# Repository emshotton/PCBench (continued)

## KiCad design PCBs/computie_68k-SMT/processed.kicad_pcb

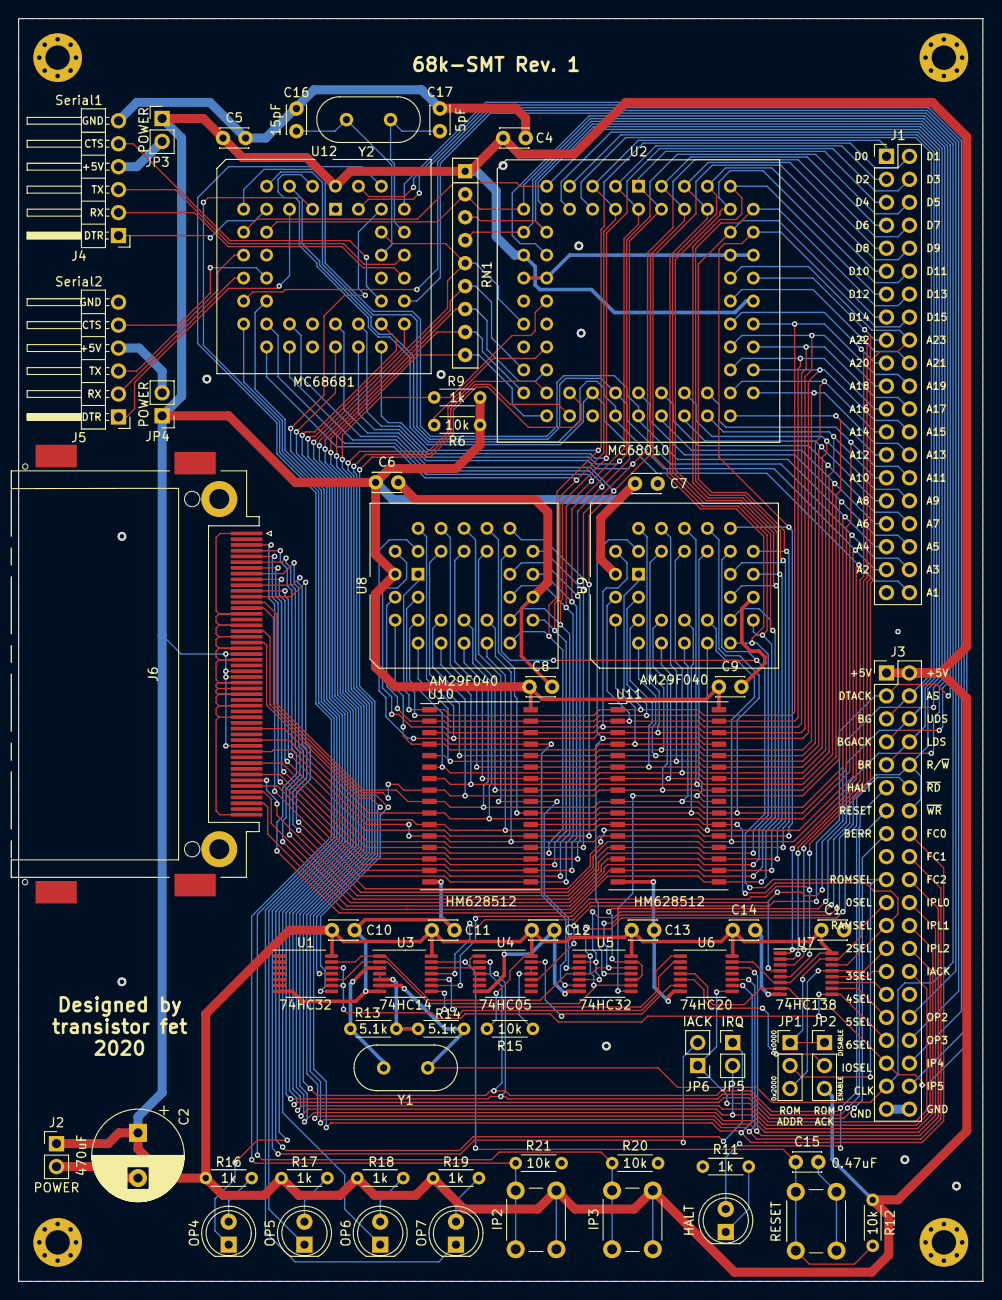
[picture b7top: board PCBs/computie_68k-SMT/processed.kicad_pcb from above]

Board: 2 copper layers, 106.7 x 139.7 mm, 68 parts (0 on the bottom side), 115 nets.

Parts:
C1, C4, C5, C6, C7, C8, C9, C10, C11, C12, C13, C14: 0.1uF; C_Disc_D3.0mm_W2.0mm_P2.50mm
C2: 470uF; CP_Radial_D10.0mm_P5.00mm
C15: 0.47uF; C_Disc_D3.0mm_W2.0mm_P2.50mm
C16: 15pF; C_Disc_D3.0mm_W2.0mm_P2.50mm
C17: 5pF; C_Disc_D3.0mm_W2.0mm_P2.50mm
D1: HALT; LED_D5.0mm
D2: OP4; LED_D5.0mm
D3: OP5; LED_D5.0mm
D4: OP6; LED_D5.0mm
D5: OP7; LED_D5.0mm
H1, H2, H3, H4: .; MountingHole_2.7mm_Pad_Via
J1: ADBUS; PinHeader_2x20_P2.54mm_Vertical
J2: POWER; PinHeader_1x02_P2.54mm_Vertical
J3: SIGBUS; PinHeader_2x20_P2.54mm_Vertical
J4: Serial1; PinHeader_1x06_P2.54mm_Horizontal
J5: Serial2; PinHeader_1x06_P2.54mm_Horizontal
J6: CompactFlash; CF-Card_3M_N7E50-Q516RB-40
JP1: ROMJMP; PinHeader_1x03_P2.54mm_Vertical
JP2: ROMACK; PinHeader_1x03_P2.54mm_Vertical
JP3, JP4: POWER; PinHeader_1x02_P2.54mm_Vertical
JP5: IRQ; PinHeader_1x02_P2.54mm_Vertical
JP6: IACK; PinHeader_1x02_P2.54mm_Vertical
R6, R12, R15, R20, R21: 10k; R_Axial_DIN0204_L3.6mm_D1.6mm_P5.08mm_Horizontal
R9, R11, R16, R17, R18, R19: 1k; R_Axial_DIN0204_L3.6mm_D1.6mm_P5.08mm_Horizontal
R13, R14: 5.1k; R_Axial_DIN0204_L3.6mm_D1.6mm_P5.08mm_Horizontal
RN1: 10k; R_Array_SIP9
SW1: RESET; SW_PUSH_6mm
SW2: IP2; SW_PUSH_6mm
SW3: IP3; SW_PUSH_6mm
U1, U5: 74HC32; TSSOP-14_4.4x5mm_P0.65mm
U2: MC68010; PLCC-68_THT-Socket
U3: 74HC14; TSSOP-14_4.4x5mm_P0.65mm
U4: 74HC05; TSSOP-14_4.4x5mm_P0.65mm
U6: 74HC20; TSSOP-14_4.4x5mm_P0.65mm
U7: 74HC138; TSSOP-16_4.4x5mm_P0.65mm
U8, U9: AM29F040; PLCC-32_THT-Socket
U10, U11: HM628512; TSOP-II-32_21.0x10.2mm_P1.27mm
U12: MC68681; PLCC-44_THT-Socket
Y1, Y2: Crystal; Crystal_HC49-4H_Vertical

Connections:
0SEL: J3.21, JP1.1, JP2.1, U7.15
2SEL: J3.25, JP1.3, U7.13
3SEL: J3.27, U7.12
4SEL: J3.29, U7.11
5SEL: J3.31, U7.10
6SEL: J3.33, U1.9, U1.12, U7.9
+5V: C1.1, C2.1, C4.1, C5.1, C6.1, C7.1, C8.1, C9.1, C10.1, C11.1, C12.1, C13.1, C14.1, J2.1, J3.1, J3.2, J6.13, J6.36, J6.38, J6.44, JP2.3, JP3.1, JP4.1, R6.1, R9.1, R12.1, R15.1, R16.2, R17.2, R18.2, R19.2, RN1.1, SW2.2, SW3.2, U1.14, U2.14, U2.52, U3.14, U4.14, U5.14, U6.13, U6.14, U7.6, U7.16, U8.32, U9.32, U10.32, U11.32, U12.44
A1: J1.40, J6.20, U2.32, U8.12, U9.12, U10.12, U11.12, U12.2
A2: J1.37, J6.19, U2.33, U8.11, U9.11, U10.11, U11.11, U12.4
A3: J1.38, J6.18, U2.34, U8.10, U9.10, U10.10, U11.10, U12.6
A4: J1.35, J6.7, U2.35, U8.9, U9.9, U10.9, U11.9, U12.7
A5: J1.36, J6.32, U2.36, U8.8, U9.8, U10.8, U11.8
A6: J1.33, U2.37, U8.7, U9.7, U10.7, U11.7
A7: J1.34, U2.38, U8.6, U9.6, U10.6, U11.6
A8: J1.31, U2.39, U8.5, U9.5, U10.5, U11.5
A9: J1.32, U2.40, U8.27, U9.27, U10.27, U11.27
A10: J1.29, U2.41, U8.26, U9.26, U10.26, U11.26
A11: J1.30, U2.42, U8.23, U9.23, U10.23, U11.23
A12: J1.27, U2.43, U8.25, U9.25, U10.25, U11.25
A13: J1.28, U2.44, U8.4, U9.4, U10.4, U11.4
A14: J1.25, U2.45, U8.28, U9.28, U10.28, U11.28
A15: J1.26, U2.46, U8.29, U9.29, U10.3, U11.3
A16: J1.23, U2.47, U8.3, U9.3, U10.31, U11.31
A17: J1.24, U2.48, U8.2, U9.2, U10.2, U11.2
A18: J1.21, U2.49, U8.30, U9.30, U10.30, U11.30
A19: J1.22, U2.50, U8.1, U9.1, U10.1, U11.1
A20: J1.19, U2.51, U7.1
A21: J1.20, U2.53, U7.2
A22: J1.17, U2.54, U7.3
A23: J1.18, U2.55, U3.9, U7.5
AS: J3.4, U2.6, U3.11, U7.4
BERR: J3.15, RN1.6, U2.24
BG: J3.5, U2.11
BGACK: J3.7, RN1.4, U2.12
BR: J3.9, RN1.3, U2.13
CLK: J3.37, R14.1, U2.15, U3.6, Y1.2
D0: J1.1, J6.21, U2.5, U8.13, U10.13, U12.28
D1: J1.2, J6.22, U2.4, U8.14, U10.14, U12.18
D2: J1.3, J6.23, U2.3, U8.15, U10.15, U12.27
D3: J1.4, J6.2, U2.2, U8.17, U10.17, U12.19
D4: J1.5, J6.3, U2.1, U8.18, U10.18, U12.26
D5: J1.6, J6.4, U2.68, U8.19, U10.19, U12.20
D6: J1.7, J6.5, U2.67, U8.20, U10.20, U12.25
D7: J1.8, J6.6, U2.66, U8.21, U10.21, U12.21
D8: J1.9, J6.47, U2.65, U9.13, U11.13
D9: J1.10, J6.48, U2.64, U9.14, U11.14
D10: J1.11, J6.49, U2.63, U9.15, U11.15
D11: J1.12, J6.27, U2.62, U9.17, U11.17
D12: J1.13, J6.28, U2.61, U9.18, U11.18
D13: J1.14, J6.29, U2.60, U9.19, U11.19
D14: J1.15, J6.30, U2.59, U9.20, U11.20
D15: J1.16, J6.31, U2.58, U9.21, U11.21
DTACK: J3.3, RN1.2, U2.10, U4.10, U12.10
FC0: J3.16, U2.30, U6.9
FC1: J3.18, U2.29, U6.10
FC2: J3.20, U2.28, U6.12
GND: C1.2, C2.2, C4.2, C5.2, C6.2, C7.2, C8.2, C9.2, C10.2, C11.2, C12.2, C13.2, C14.2, C15.2, C16.1, C17.1, J2.2, J3.39, J3.40, J4.6, J5.6, J6.1, J6.8, J6.9, J6.10, J6.11, J6.12, J6.14, J6.15, J6.16, J6.17, J6.39, J6.50, R11.2, R20.2, R21.2, SW1.1, U1.7, U2.16, U2.17, U2.56, U2.57, U3.7, U4.7, U5.7, U6.7, U7.8, U8.16, U9.16, U10.16, U11.16, U12.22
HALT: D1.2, J3.11, R9.2, U2.19, U4.2
IACK: J3.28, JP6.1, U6.8
IORD: J6.34, U1.8
IOSEL: J3.35, U6.4, U7.7, U12.39
IOWR: J6.35, U1.11
IP4: J3.36, U12.43
IP5: J3.38, U12.42
IPL0: J3.22, RN1.9, U2.27
IPL1: J3.24, JP5.2, RN1.8, U2.26
IPL2: J3.26, RN1.7, U2.25
LDS: J3.8, U2.8, U5.2, U5.5
unnamed: C15.1, R12.2, SW1.2, U3.13
unnamed: C16.2, U12.36, Y2.2
unnamed: C17.2, U12.37, Y2.1
unnamed: D1.1, R11.1
unnamed: D2.1, U12.30
unnamed: D2.2, R16.1
unnamed: D3.1, U12.16
unnamed: D3.2, R17.1
unnamed: D4.1, U12.29
unnamed: D4.2, R18.1
unnamed: D5.1, U12.17
unnamed: D5.2, R19.1
unnamed: J4.1, U12.8
unnamed: J4.2, U12.33
unnamed: J4.3, U12.35
unnamed: J4.4, JP3.2
unnamed: J4.5, U12.32
unnamed: J5.1, U12.5
unnamed: J5.2, U12.13
unnamed: J5.3, U12.11
unnamed: J5.4, JP4.2
unnamed: J5.5, U12.14
unnamed: JP2.2, U6.5
unnamed: R6.2, U2.23
unnamed: R13.1, R14.2, U3.4, U3.5
unnamed: R13.2, U3.3, Y1.1
unnamed: R15.2, U4.11, U4.12
unnamed: R20.1, SW3.1, U12.3
unnamed: R21.1, SW2.1, U12.40
unnamed: U3.8, U6.2
unnamed: U3.10, U6.1
unnamed: U3.12, U4.1, U4.3
unnamed: U4.13, U6.6
OP2: J3.32, U12.31
OP3: J3.34, U12.15
RAMSEL: J3.23, U7.14, U10.22, U11.22
RD: J3.12, U1.10, U3.2, U5.1, U5.9
RD-L: U5.3, U8.24, U10.24
RD-U: U5.8, U9.24, U11.24
RESET: J3.13, RN1.5, U2.20, U4.4, U12.38
ROMSEL: J3.19, JP1.2, U8.22, U9.22
R~W: J3.10, J3.14, U1.13, U2.9, U3.1, U5.4, U5.12, U12.9
SIACK: JP6.2, U12.41
SIRQ: JP5.1, U12.24
UDS: J3.6, U2.7, U5.10, U5.13
WR-L: U5.6, U8.31, U10.29
WR-U: U5.11, U9.31, U11.29
